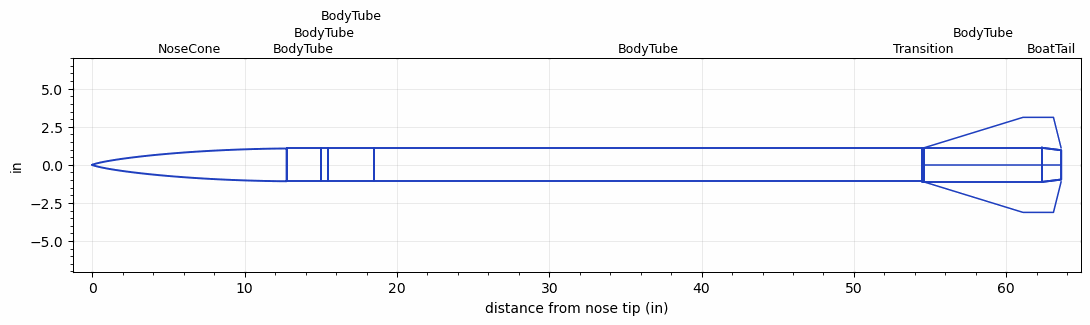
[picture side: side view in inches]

<RASAeroDocument>
 <FileVersion>2</FileVersion>
 <RocketDesign>
  <NoseCone>
   <Length>12.75</Length>
   <Diameter>2.15</Diameter>
   <Shape>LV-Haack</Shape>
   <Location>0</Location>
  </NoseCone>
  <BodyTube>
   <Length>2.25</Length>
   <Diameter>2.15</Diameter>
   <Location>12.75</Location>
  </BodyTube>
  <BodyTube>
   <Length>0.5</Length>
   <Diameter>2.15</Diameter>
   <Location>15</Location>
  </BodyTube>
  <BodyTube>
   <Length>3</Length>
   <Diameter>2.15</Diameter>
   <Location>15.5</Location>
  </BodyTube>
  <BodyTube>
   <Length>36</Length>
   <Diameter>2.15</Diameter>
   <Location>18.5</Location>
  </BodyTube>
  <Transition>
   <Length>0.1</Length>
   <Diameter>2.24</Diameter>
   <Location>54.5</Location>
   <RearDiameter>2.24</RearDiameter>
  </Transition>
  <BodyTube>
   <Length>7.75</Length>
   <Diameter>2.24</Diameter>
   <Location>54.6</Location>
   <BoattailLength>1.255</BoattailLength>
   <BoattailRearDiameter>1.926</BoattailRearDiameter>
   <Overhang>1.25</Overhang>
   <Fin>
    <Count>4</Count>
    <Chord>9</Chord>
    <Span>2</Span>
    <SweepDistance>6.5</SweepDistance>
    <TipChord>2</TipChord>
    <Thickness>0.125</Thickness>
    <LERadius>0.05</LERadius>
    <Location>7.75</Location>
    <AirfoilSection>Hexagonal</AirfoilSection>
    <FX1>0.25</FX1>
    <FX3>0.25</FX3>
   </Fin>
  </BodyTube>
  <BoatTail>
   <Length>1.255</Length>
   <Diameter>2.24</Diameter>
   <RearDiameter>1.926</RearDiameter>
   <Location>62.35</Location>
  </BoatTail>
  <Surface>Smooth Paint</Surface>
  <ModifiedBarrowman>True</ModifiedBarrowman>
  <Turbulence>True</Turbulence>
  <UseBooster1>False</UseBooster1>
  <UseBooster2>False</UseBooster2>
 </RocketDesign>
 <LaunchSite>
  <Altitude>4000</Altitude>
  <Pressure>0</Pressure>
  <RodAngle>2</RodAngle>
  <RodLength>10</RodLength>
  <Temperature>85</Temperature>
  <WindSpeed>10</WindSpeed>
 </LaunchSite>
 <Recovery>
  <Altitude1>1000</Altitude1>
  <Altitude2>1000</Altitude2>
  <DeviceType1>None</DeviceType1>
  <DeviceType2>None</DeviceType2>
  <Event1>False</Event1>
  <Event2>False</Event2>
  <Size1>1</Size1>
  <Size2>1</Size2>
  <EventType1>None</EventType1>
  <EventType2>None</EventType2>
  <CD1>1.33</CD1>
  <CD2>1.33</CD2>
 </Recovery>
 <SimulationList>
  <Simulation>
   <SustainerEngine>M1378LR  (Loki)</SustainerEngine>
   <SustainerLaunchWt>11.2</SustainerLaunchWt>
   <SustainerNozzleDiameter>1.5</SustainerNozzleDiameter>
   <SustainerCG>39.25</SustainerCG>
   <SustainerIgnitionDelay>0</SustainerIgnitionDelay>
   <Booster1SeparationDelay>0</Booster1SeparationDelay>
   <Booster1IgnitionDelay>0</Booster1IgnitionDelay>
   <IncludeBooster1>False</IncludeBooster1>
   <Booster2Delay>0</Booster2Delay>
   <IncludeBooster2>False</IncludeBooster2>
   <TimetoApogee>44.05861</TimetoApogee>
   <MaxAltitude>47154.84</MaxAltitude>
   <MaxVelocity>3709.038</MaxVelocity>
   <OptimumWt>12.18</OptimumWt>
   <OptimumMaxAlt>12.18</OptimumMaxAlt>
  </Simulation>
 </SimulationList>
</RASAeroDocument>
